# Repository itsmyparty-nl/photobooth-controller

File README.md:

# Photobooth Controller #

The hardware side of the photobooth

### What is this repository for? ###

* PCB Board & Corresponding Firmware to handle hardware buttons and lights for the photobooth 

### How do I get set up? ###

* Install Arduino
* Select correct library folder

### Contribution guidelines ###

* Writing tests
* Code review
* Other guidelines

### Who do I talk to? ###

* Patrick@itsmyparty.nl

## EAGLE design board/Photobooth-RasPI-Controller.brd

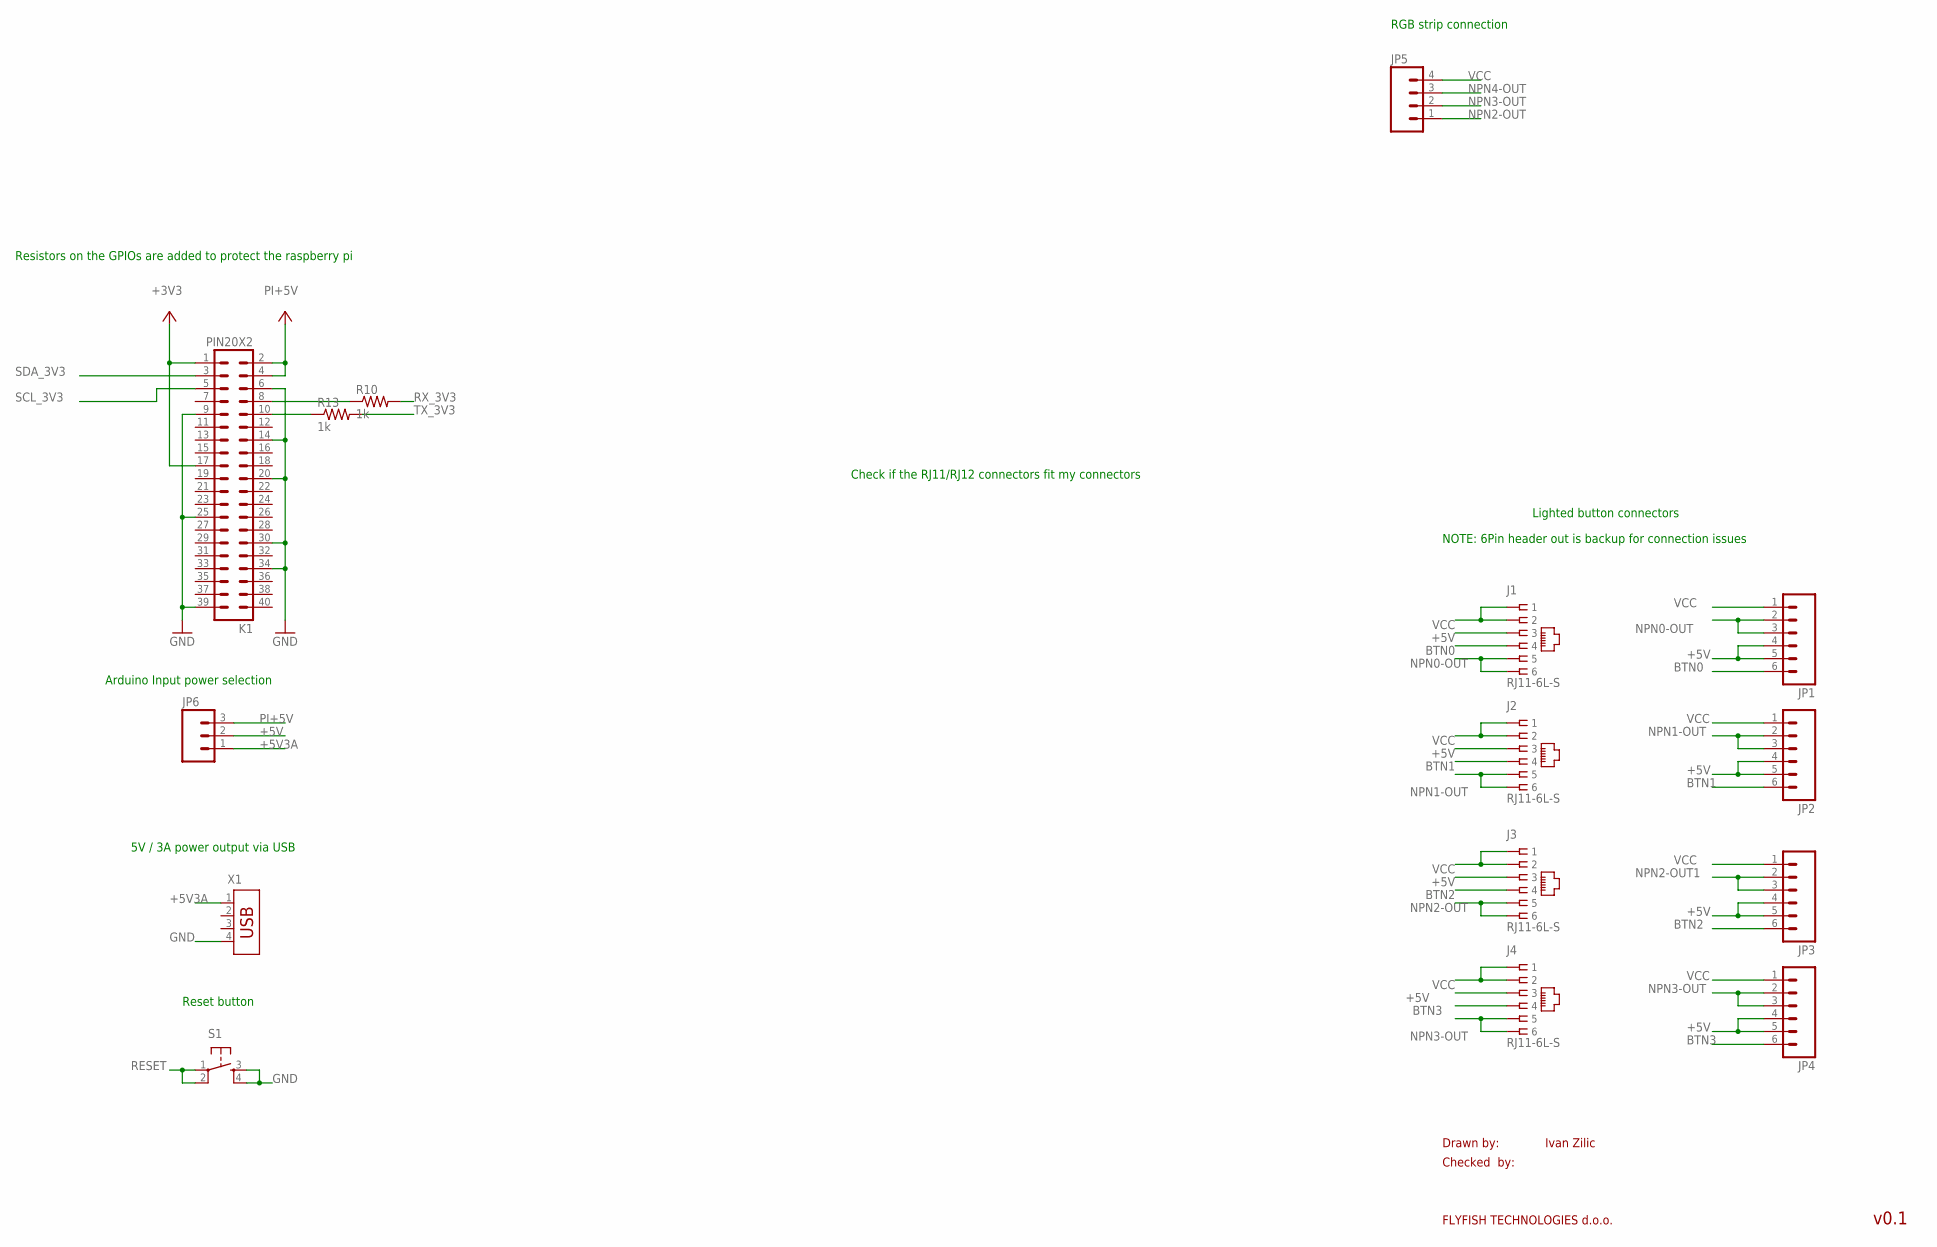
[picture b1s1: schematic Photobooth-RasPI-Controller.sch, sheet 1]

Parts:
J1, J2, J3, J4: RJ11-6L-S; RJ11-NO_SHIELD
JP1, JP2, JP3, JP4: M06LOCK; 1X06_LOCK
JP5: M04LOCK; 1X04_LOCK
JP6: M03LOCK; 1X03_LOCK
K1: PIN20X2; PIN_20X2
R10, R13: 1k; 0805
S1: TAC_SWITCHPTH; TACTILE-PTH
X1: USB-787616; USB

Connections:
+3V3: K1.1, K1.17; also elsewhere on the board
+5V: J1.3, J2.3, J3.3, J4.3, JP1.4, JP1.5, JP2.4, JP2.5, JP3.4, JP3.5, JP4.4, JP4.5, JP6.2; also elsewhere on the board
+5V3A: JP6.1, X1.1; also elsewhere on the board
BTN0: J1.4, JP1.6; also elsewhere on the board
BTN1: J2.4, JP2.6; also elsewhere on the board
BTN2: J3.4, JP3.6; also elsewhere on the board
BTN3: J4.4, JP4.6; also elsewhere on the board
GND: K1.6, K1.9, K1.14, K1.20, K1.25, K1.30, K1.34, K1.39, S1.3, S1.4, X1.4; also elsewhere on the board
unnamed: K1.8, R10.1
unnamed: K1.10, R13.1
NPN0-OUT: J1.5, J1.6, JP1.2, JP1.3; also elsewhere on the board
NPN1-OUT: J2.5, J2.6, JP2.2, JP2.3; also elsewhere on the board
NPN2-OUT: J3.5, J3.6, JP5.1; also elsewhere on the board
NPN2-OUT1: JP3.2, JP3.3
NPN3-OUT: J4.5, J4.6, JP4.2, JP4.3, JP5.2; also elsewhere on the board
NPN4-OUT: JP5.3; also elsewhere on the board
PI+5V: JP6.3, K1.2, K1.4
RESET: S1.1, S1.2; also elsewhere on the board
RX_3V3: R10.2; also elsewhere on the board
SCL_3V3: K1.5; also elsewhere on the board
SDA_3V3: K1.3; also elsewhere on the board
TX_3V3: R13.2; also elsewhere on the board
VCC: J1.1, J1.2, J2.1, J2.2, J3.1, J3.2, J4.1, J4.2, JP1.1, JP2.1, JP3.1, JP4.1, JP5.4; also elsewhere on the board

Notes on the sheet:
Drawn by:
Checked by:
FLYFISH TECHNOLOGIES d.o.o.
Ivan Zilic
v0.1
5V / 3A power output via USB
Resistors on the GPIOs are added to protect the raspberry pi
Check if the RJ11/RJ12 connectors fit my connectors
RGB strip connection
Lighted button connectors
NOTE: 6Pin header out is backup for connection issues
Arduino Input power selection
Reset button

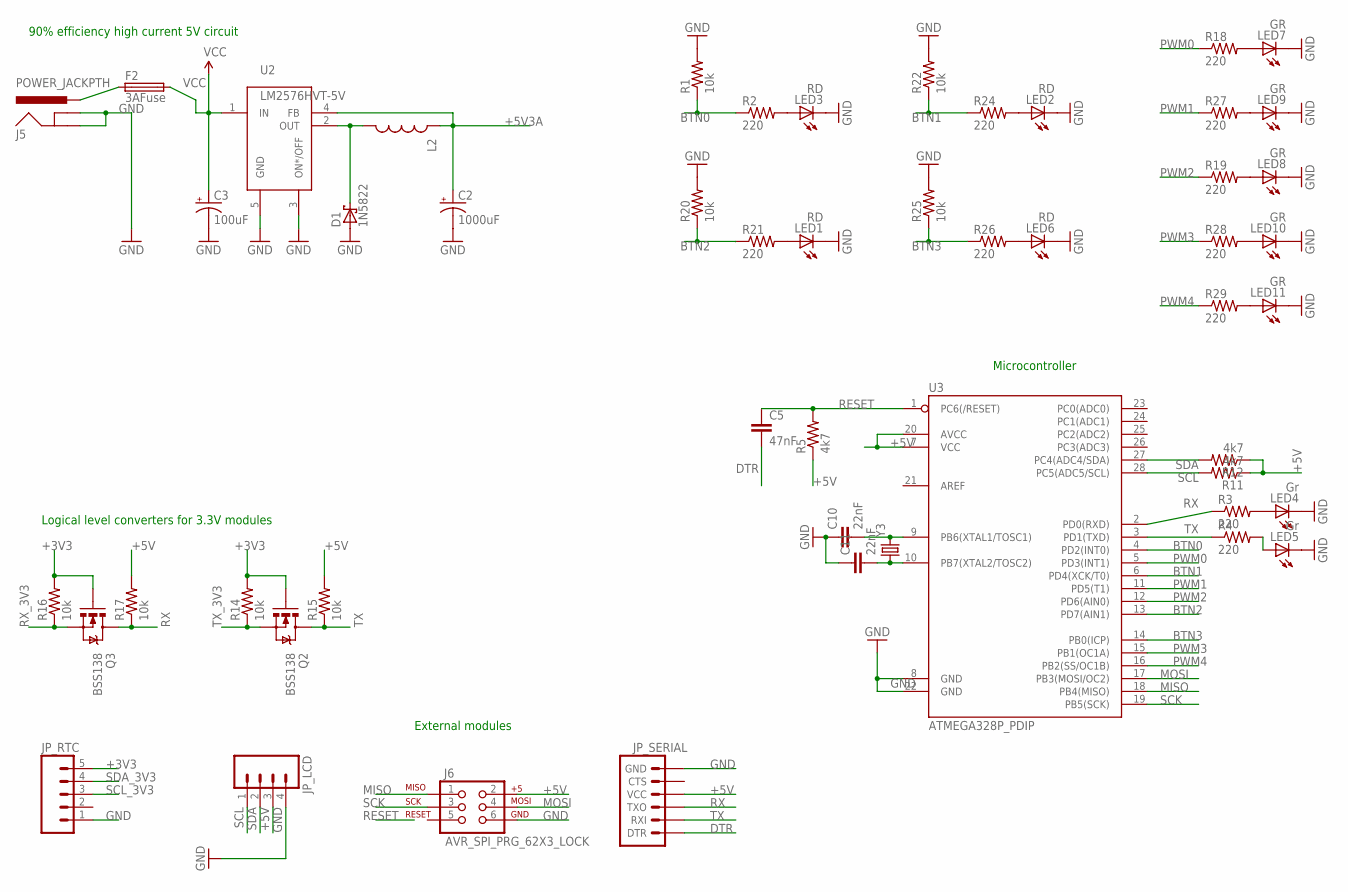
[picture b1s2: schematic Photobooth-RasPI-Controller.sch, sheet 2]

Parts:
C2: 1000uF; CPOL-RADIAL-1000UF-25V
C3: 100uF; CPOL-RADIAL-100UF-25V
C5: 47nF; CAP-PTH-SMALL
C10, C11: 22nF; CAP-PTH-SMALL
D1: 1N5822; C4111-15
F2: 3AFuse; LITTLEFUSE
J5: POWER_JACKPTH; POWER_JACK_PTH
J6: AVR_SPI_PRG_62X3_LOCK; 2X3_LOCK
JP_LCD: M04PTH; 1X04
JP_RTC: M05LOCK; 1X05_LOCK
JP_SERIAL: ARDUINO_SERIAL_PROGRAMLOCK; 1X06_LOCK
L2: INDUCTORRLB0912; RLB0912
LED1, LED2, LED3, LED6: RD; CHIP-LED0805
LED4, LED5: Gr; CHIP-LED0805
LED7, LED8, LED9, LED10, LED11: GR; CHIP-LED0805
Q2, Q3: BSS138; SOT23-3
R1, R14, R15, R16, R17, R20, R22, R25: 10k; 0805
R2, R3, R4, R18, R19, R21, R24, R26, R27, R28, R29: 220; 0805
R5, R11, R12: 4k7; 0805
U2: LM2576HVT-5V; LM2576
U3: ATMEGA328P_PDIP; DIL28-3
Y3: CRYSTALHC49UV; HC49U-V

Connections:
+3V3: JP_RTC.5, Q2.1 (G), Q3.1 (G), R14.2, R16.2; also elsewhere on the board
+5V: J6.2, JP_LCD.3, JP_SERIAL.4 (VCC), R5.1, R11.1, R12.1, R15.2, R17.2, U3.7 (VCC), U3.20 (AVCC); also elsewhere on the board
+5V3A: C2.+, L2.1, U2.4 (FB); also elsewhere on the board
BTN0: R1.1, R2.1, U3.4 (PD2(INT0)); also elsewhere on the board
BTN1: R22.1, R24.1, U3.6 (PD4(XCK/T0)); also elsewhere on the board
BTN2: R20.1, R21.1, U3.13 (PD7(AIN1)); also elsewhere on the board
BTN3: R25.1, R26.1, U3.14 (PB0(ICP)); also elsewhere on the board
DTR: C5.2, JP_SERIAL.1 (DTR)
GND: C2.-, C3.2 (-), C10.1, C11.1, D1.A, J5.GND, J5.GNDBREAK, J6.6, JP_LCD.4, JP_RTC.1, JP_SERIAL.6 (GND), LED1.C, LED2.C, LED3.C, LED4.C, LED5.C, LED6.C, LED7.C, LED8.C, LED9.C, LED10.C, LED11.C, R1.2, R20.2, R22.2, R25.2, U2.3 (ON*/OFF), U2.5 (GND), U3.8 (GND), U3.22 (GND); also elsewhere on the board
MISO: J6.1, U3.18 (PB4(MISO))
MOSI: J6.4, U3.17 (PB3(MOSI/OC2))
unnamed: C11.2, U3.10 (PB7(XTAL2/TOSC2)), Y3.1
unnamed: C10.2, U3.9 (PB6(XTAL1/TOSC1)), Y3.2
unnamed: D1.C, L2.2, U2.2 (OUT)
unnamed: LED7.A, R18.2
unnamed: LED8.A, R19.2
unnamed: LED1.A, R21.2
unnamed: LED2.A, R24.2
unnamed: LED6.A, R26.2
unnamed: LED9.A, R27.2
unnamed: LED10.A, R28.2
unnamed: LED11.A, R29.2
unnamed: F2.1, J5.PWR
unnamed: LED3.A, R2.2
unnamed: LED4.A, R3.2
unnamed: LED5.A, R4.2
PWM0: R18.1, U3.5 (PD3(INT1)); also elsewhere on the board
PWM1: R27.1, U3.11 (PD5(T1)); also elsewhere on the board
PWM2: R19.1, U3.12 (PD6(AIN0)); also elsewhere on the board
PWM3: R28.1, U3.15 (PB1(OC1A)); also elsewhere on the board
PWM4: R29.1, U3.16 (PB2(SS/OC1B)); also elsewhere on the board
RESET: C5.1, R5.2, U3.1 (PC6(/RESET)); also elsewhere on the board
RX: JP_SERIAL.3 (TXO), Q3.3 (D), R3.1, R17.1, U3.2 (PD0(RXD))
RX_3V3: Q3.2 (S), R16.1; also elsewhere on the board
SCK: J6.3, U3.19 (PB5(SCK))
SCL: JP_LCD.1, R11.2, U3.28 (PC5(ADC5/SCL))
SCL_3V3: JP_RTC.3; also elsewhere on the board
SDA: JP_LCD.2, R12.2, U3.27 (PC4(ADC4/SDA))
SDA_3V3: JP_RTC.4; also elsewhere on the board
TX: JP_SERIAL.2 (RXI), Q2.3 (D), R4.1, R15.1, U3.3 (PD1(TXD))
TX_3V3: Q2.2 (S), R14.1; also elsewhere on the board
VCC: C3.1 (+), F2.2, U2.1 (IN); also elsewhere on the board

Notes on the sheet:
Logical level converters for 3.3V modules
External modules
90% efficiency high current 5V circuit
Microcontroller

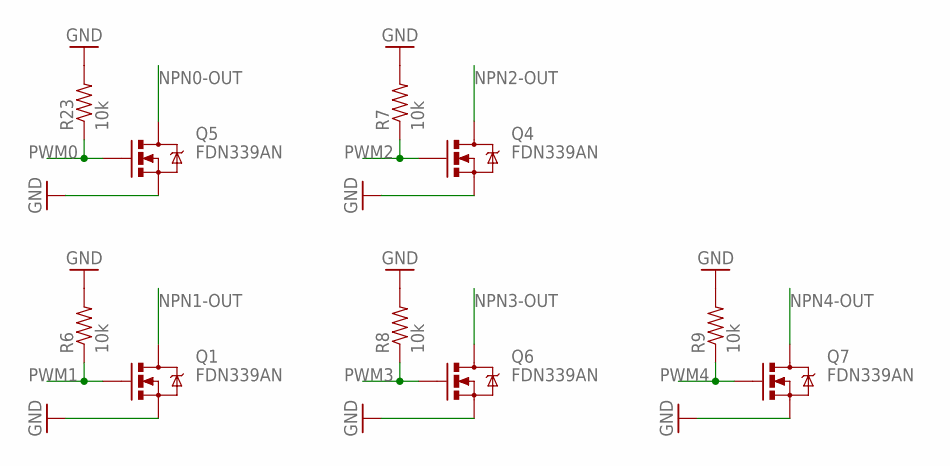
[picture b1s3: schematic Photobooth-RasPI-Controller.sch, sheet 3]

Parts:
Q1, Q4, Q5, Q6, Q7: FDN339AN; SOT23-3
R6, R7, R8, R9, R23: 10k; 0805

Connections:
GND: Q1.2 (S), Q4.2 (S), Q5.2 (S), Q6.2 (S), Q7.2 (S), R6.2, R7.2, R8.2, R9.2, R23.2; also elsewhere on the board
NPN0-OUT: Q5.3 (D); also elsewhere on the board
NPN1-OUT: Q1.3 (D); also elsewhere on the board
NPN2-OUT: Q4.3 (D); also elsewhere on the board
NPN3-OUT: Q6.3 (D); also elsewhere on the board
NPN4-OUT: Q7.3 (D); also elsewhere on the board
PWM0: Q5.1 (G), R23.1; also elsewhere on the board
PWM1: Q1.1 (G), R6.1; also elsewhere on the board
PWM2: Q4.1 (G), R7.1; also elsewhere on the board
PWM3: Q6.1 (G), R8.1; also elsewhere on the board
PWM4: Q7.1 (G), R9.1; also elsewhere on the board

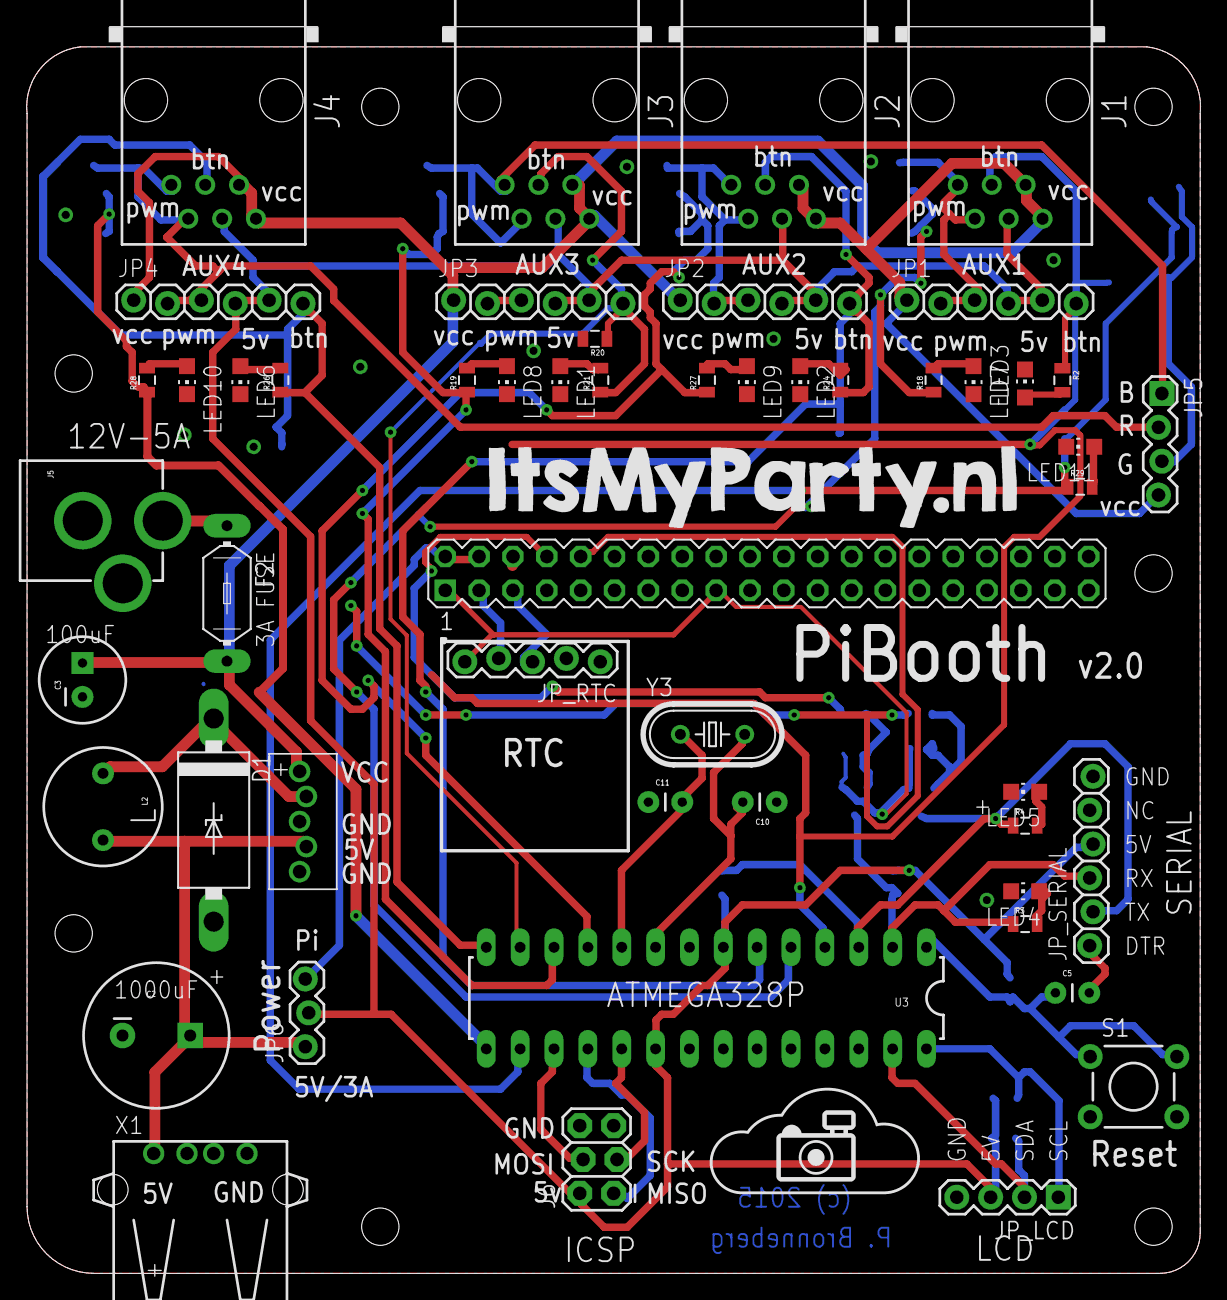
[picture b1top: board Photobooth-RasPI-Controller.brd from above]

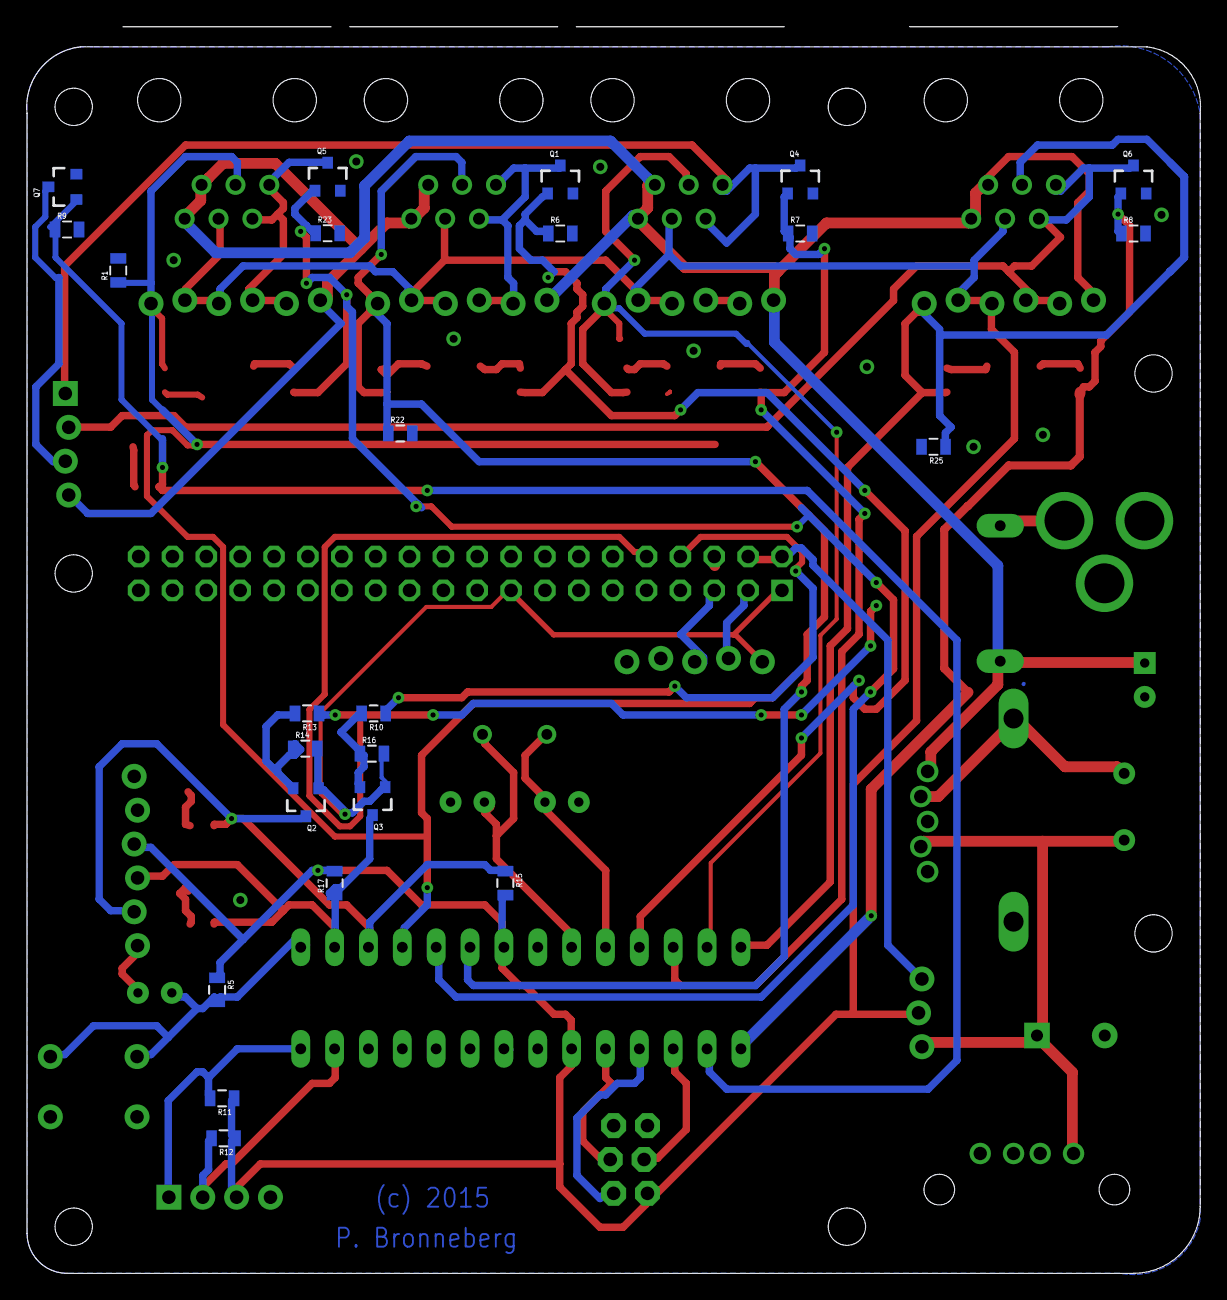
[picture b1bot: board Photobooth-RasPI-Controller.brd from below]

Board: 2 copper layers, 88.0 x 93.5 mm, 76 parts (24 on the bottom side), 51 nets.

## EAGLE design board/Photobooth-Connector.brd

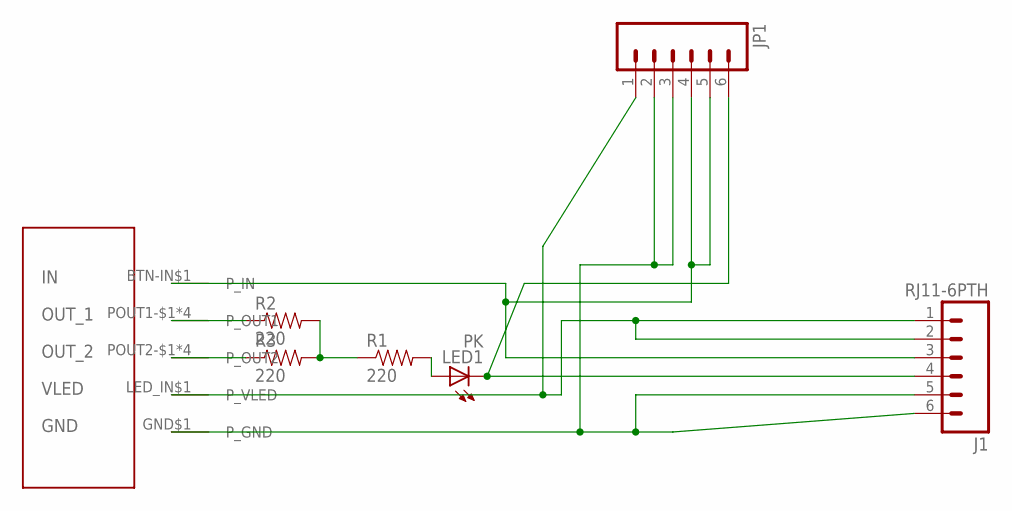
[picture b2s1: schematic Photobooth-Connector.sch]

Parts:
J1: RJ11-6PTH; RJ11-6
JP1: M06LOCK; 1X06_LOCK
LED1: PK; CHIP-LED0805
R1, R2, R3: 220; 0805
U$1: KERMIS_BUTTON; SLOT_DRILLED

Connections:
unnamed: J1.3, JP1.4, JP1.5, U$1.BTN-IN$1 (P_IN)
unnamed: J1.4, JP1.6, LED1.C
unnamed: R1.1, R2.2, R3.2
unnamed: LED1.A, R1.2
unnamed: J1.1, J1.2, JP1.1, U$1.LED_IN$1 (P_VLED)
unnamed: J1.5, J1.6, JP1.2, JP1.3, U$1.GND$1 (P_GND)
unnamed: R2.1, U$1.POUT1-$1 (P_OUT1), U$1.POUT1-$2 (P_OUT1), U$1.POUT1-$3 (P_OUT1), U$1.POUT1-$4 (P_OUT1)
unnamed: R3.1, U$1.POUT2-$1 (P_OUT2), U$1.POUT2-$2 (P_OUT2), U$1.POUT2-$3 (P_OUT2), U$1.POUT2-$4 (P_OUT2)

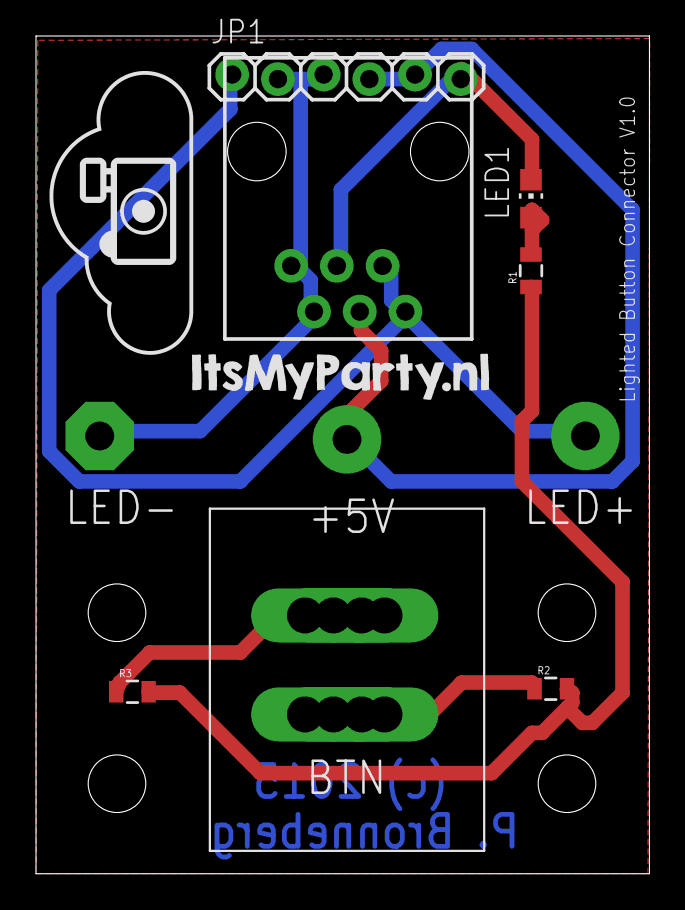
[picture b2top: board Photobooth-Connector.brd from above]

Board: 2 copper layers, 34.1 x 46.5 mm, 7 parts (0 on the bottom side), 8 nets.

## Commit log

2017-08-06 Add existing arduino code and eagle PCB
2017-08-06 README.md created online with Bitbucket

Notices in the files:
board/Photobooth-Connector.brd:
(c) 2015
parts and their libraries:
SparkFun-Connectors: Licensing: Creative Commons ShareAlike 4.0 International - https://creativecommons.org/licenses/by-sa/4.0
